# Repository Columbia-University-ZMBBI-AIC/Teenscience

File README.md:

# TeenScience
TennScience Platform
TennScience is a hardware and software platform based in Arduino and Teensy 3.6 for science research involving behavioral neuroscience, robotics, sound analysis, and more.
Testing Hardware

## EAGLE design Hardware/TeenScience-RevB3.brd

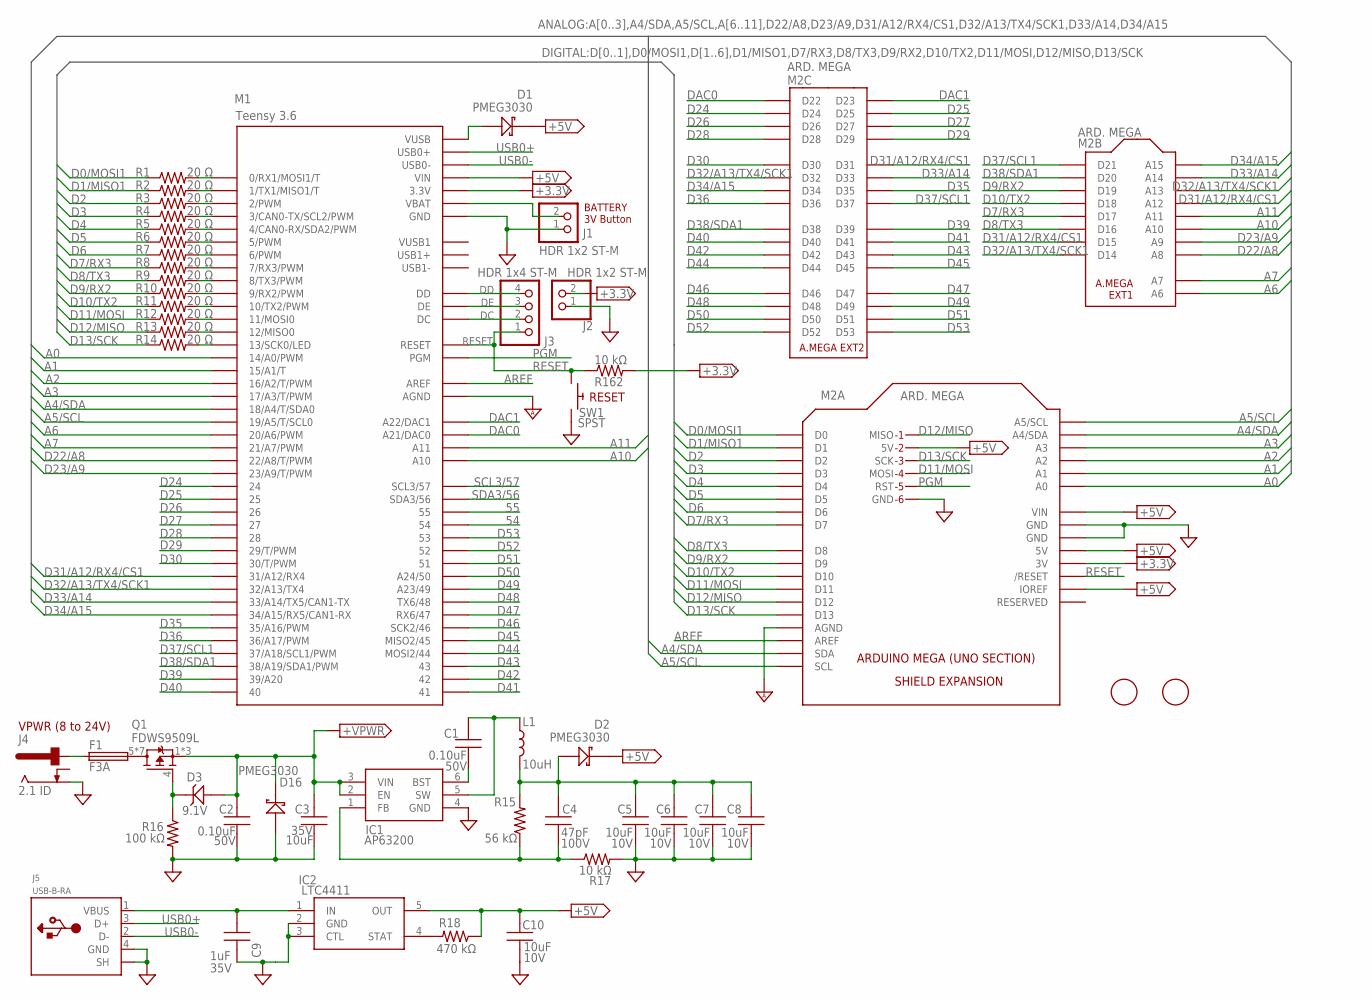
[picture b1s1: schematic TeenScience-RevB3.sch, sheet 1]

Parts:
C1, C2: 0.10uF; MLCC_0603
C3: 10uF; MLCC_1206
C4: 47pF; MLCC_0603
C5, C6, C7, C8, C10: 10uF; MLCC_0603
C9: 1uF; MLCC_0603
D1, D2, D16: PMEG3030; SOD_128_DIODE
D3: 9.1V; SOD3716X135N_DIODE
F1: F3A; 1206-3.2X1.6MM
IC1: AP63200; SOT95P280X100-6N
IC2: LTC4411; SOT95P280X100-5N
J1, J2: HDR 1x2 ST-M; HDR_1X2
J3: HDR 1x4 ST-M; HDR_1X04
J4: 2.1 ID; DCJACK-721RA
J5: USB-B-RA; USB-B
L1: 10uH; IND_5X5MM-5045
M1: Teensy 3.6; TEENSY_3.6_ALL_PINS&PADS
M2: ARD. MEGA; ARDUINO_MEGA_ICSP
Q1: FDWS9509L; FDN8_5.1X6.3
R1, R2, R3, R4, R5, R6, R7, R8, R9, R10, R11, R12, R13, R14: 20 Ω; R0603
R15: 56 kΩ; R0603
R16: 100 kΩ; R0603
R17, R162: 10 kΩ; R0603
R18: 470 kΩ; R0603
SW1: SPST; SWITCH_TAC_6MM
U$3, U$6: FIDUCIAL; FIDUCIAL_1MM

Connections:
54: M1.54; also elsewhere on the board
55: M1.55; also elsewhere on the board
+3.3V: J2.2, M1.3.3V, M1.3.3V2 (3.3V), M1.3.3V3 (3.3V), M1.3.3V4 (3.3V), M2.3V, R162.2; also elsewhere on the board
+5V: C10.2, D1.1 (K), D2.1 (K), IC2.5 (OUT), M1.VIN, M2.5V, M2.5V@1 (5V), M2.5V@2 (5V), M2.5V_ICSP (5V), M2.IOREF, M2.VIN, R18.1; also elsewhere on the board
+VPWR: C2.1, C3.1, D3.2 (A), D16.1 (K), IC1.2 (EN), IC1.3 (VIN), Q1.1 (S), Q1.2 (S), Q1.3 (S); also elsewhere on the board
A0: M1.14/A0 (14/A0/PWM), M2.A0; also elsewhere on the board
A1: M1.15/A1 (15/A1/T), M2.A1; also elsewhere on the board
A2: M1.16/A2 (16/A2/T/PWM), M2.A2; also elsewhere on the board
A3: M1.17/A3 (17/A3/T/PWM), M2.A3; also elsewhere on the board
A4/SDA: M1.18/A4 (18/A4/T/SDA0), M2.A4 (A4/SDA), M2.SDA; also elsewhere on the board
A5/SCL: M1.19/A5 (19/A5/T/SCL0), M2.A5 (A5/SCL), M2.SCL; also elsewhere on the board
A6: M1.20/A6 (20/A6/PWM), M2.A6; also elsewhere on the board
A7: M1.21/A7 (21/A7/PWM), M2.A7; also elsewhere on the board
A10: M1.A10, M2.A10
A11: M1.A11, M2.A11
AREF: M1.AREF, M2.AREF; also elsewhere on the board
D0/MOSI1: M2.D0, R1.1; also elsewhere on the board
D1/MISO1: M2.D1, R2.1; also elsewhere on the board
D2: M2.D2, R3.1; also elsewhere on the board
D3: M2.D3, R4.1; also elsewhere on the board
D4: M2.D4, R5.1; also elsewhere on the board
D5: M2.D5, R6.1; also elsewhere on the board
D6: M2.D6, R7.1; also elsewhere on the board
D7/RX3: M2.D7, M2.D17, R8.1; also elsewhere on the board
D8/TX3: M2.D8, M2.D16, R9.1; also elsewhere on the board
D9/RX2: M2.D9, M2.D19, R10.1; also elsewhere on the board
D10/TX2: M2.D10, M2.D18, R11.1; also elsewhere on the board
D11/MOSI: M2.D11, M2.MOSI, R12.1; also elsewhere on the board
D12/MISO: M2.D12, M2.MISO, R13.1; also elsewhere on the board
D13/SCK: M2.D13, M2.SCK, R14.1; also elsewhere on the board
D22/A8: M1.22/A8 (22/A8/T/PWM), M2.A8; also elsewhere on the board
D23/A9: M1.23/A9 (23/A9/T/PWM), M2.A9; also elsewhere on the board
D24: M1.24, M2.D24; also elsewhere on the board
D25: M1.25, M2.D25; also elsewhere on the board
D26: M1.26, M2.D26; also elsewhere on the board
D27: M1.27, M2.D27; also elsewhere on the board
D28: M1.28, M2.D28; also elsewhere on the board
D29: M1.29 (29/T/PWM), M2.D29; also elsewhere on the board
D30: M1.30 (30/T/PWM), M2.D30; also elsewhere on the board
D31/A12/RX4/CS1: M1.31/A12 (31/A12/RX4), M2.A12, M2.D15, M2.D31; also elsewhere on the board
D32/A13/TX4/SCK1: M1.32/A13 (32/A13/TX4), M2.A13, M2.D14, M2.D32; also elsewhere on the board
D33/A14: M1.33/A14 (33/A14/TX5/CAN1-TX), M2.A14, M2.D33; also elsewhere on the board
D34/A15: M1.34/A15 (34/A15/RX5/CAN1-RX), M2.A15, M2.D34; also elsewhere on the board
D35: M1.35/A16 (35/A16/PWM), M2.D35; also elsewhere on the board
D36: M1.36/A17 (36/A17/PWM), M2.D36; also elsewhere on the board
D37/SCL1: M1.37/A18 (37/A18/SCL1/PWM), M2.D21, M2.D37; also elsewhere on the board
D38/SDA1: M1.38/A19 (38/A19/SDA1/PWM), M2.D20, M2.D38; also elsewhere on the board
D39: M1.39/A20, M2.D39; also elsewhere on the board
D40: M1.40, M2.D40; also elsewhere on the board
D41: M1.41, M2.D41; also elsewhere on the board
D42: M1.42, M2.D42; also elsewhere on the board
D43: M1.43, M2.D43; also elsewhere on the board
D44: M1.44 (MOSI2/44), M2.D44; also elsewhere on the board
D45: M1.45 (MISO2/45), M2.D45; also elsewhere on the board
D46: M1.46 (SCK2/46), M2.D46; also elsewhere on the board
D47: M1.47 (RX6/47), M2.D47; also elsewhere on the board
D48: M1.48 (TX6/48), M2.D48; also elsewhere on the board
D49: M1.49 (A23/49), M2.D49; also elsewhere on the board
D50: M1.50 (A24/50), M2.D50; also elsewhere on the board
D51: M1.51, M2.D51; also elsewhere on the board
D52: M1.52, M2.D52; also elsewhere on the board
D53: M1.53, M2.D53; also elsewhere on the board
DAC0: M1.A21 (A21/DAC0), M2.D22; also elsewhere on the board
DAC1: M1.A22 (A22/DAC1), M2.D23; also elsewhere on the board
DC: J3.2, M1.DC
DD: J3.4, M1.DD
DE: J3.3, M1.DE
GND: C2.2, C3.2, C5.1, C6.1, C7.1, C8.1, C9.2, C10.1, D16.2 (A), IC1.4 (GND), IC2.2 (GND), IC2.3 (CTL), J1.1, J2.1, J4.2 (SLEEVE), J5.4 (GND), J5.5 (SH), J5.6 (SH), M1.GND, M1.GND1 (GND), M1.GND2 (GND), M1.GND3 (GND), M1.GND4 (GND), M1.GND5 (GND), M1.GND6 (GND), M2.GND@1 (GND), M2.GND@2 (GND), M2.GND@3 (GND), M2.GND@4 (GND), M2.GND@5 (GND), R16.2, R17.2, SW1.3, SW1.4; also elsewhere on the board
GND_A: M1.AGND, M2.AGND; also elsewhere on the board
unnamed: D1.2 (A), M1.VUSB
unnamed: C9.1, IC2.1 (IN), J5.1 (VBUS)
unnamed: IC2.4 (STAT), R18.2
unnamed: J1.2, M1.VBAT
unnamed: F1.1, J4.1 (CENTER)
unnamed: C4.2, C5.2, C6.2, C7.2, C8.2, D2.2 (A), L1.2, R15.2
unnamed: F1.2, Q1.5 (D), Q1.6 (D), Q1.7 (D), Q1.8 (D), Q1.9 (D), Q1.10 (D), Q1.11 (D)
unnamed: D3.1 (K), Q1.4 (G), R16.1
unnamed: C1.2, IC1.5 (SW), L1.1
unnamed: C4.1, IC1.1 (FB), R15.1, R17.1
unnamed: C1.1, IC1.6 (BST)
unnamed: M1.13 (13/SCK0/LED), R14.2
unnamed: M1.0 (0/RX1/MOSI1/T), R1.2
unnamed: M1.1 (1/TX1/MISO1/T), R2.2
unnamed: M1.2 (2/PWM), R3.2
unnamed: M1.3 (3/CAN0-TX/SCL2/PWM), R4.2
unnamed: M1.4 (4/CAN0-RX/SDA2/PWM), R5.2
unnamed: M1.5 (5/PWM), R6.2
unnamed: M1.6 (6/PWM), R7.2
unnamed: M1.7 (7/RX3/PWM), R8.2
unnamed: M1.8 (8/TX3/PWM), R9.2
unnamed: M1.9 (9/RX2/PWM), R10.2
unnamed: M1.10 (10/TX2/PWM), R11.2
unnamed: M1.11 (11/MOSI0), R12.2
unnamed: M1.12 (12/MISO0), R13.2
PGM: M1.PGM, M2.RESET_ICSP (RST)
RESET: J3.1, M1.RESET, M2.RESET (/RESET), R162.1, SW1.1, SW1.2; also elsewhere on the board
SCL3/57: M1.57 (SCL3/57); also elsewhere on the board
SDA3/56: M1.56 (SDA3/56); also elsewhere on the board
USB0+: J5.3 (D+), M1.USB0+
USB0-: J5.2 (D-), M1.USB0-
VUSB1: M1.VUSB1

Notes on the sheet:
BATTERY 3V Button
RESET
VPWR (8 to 24V)

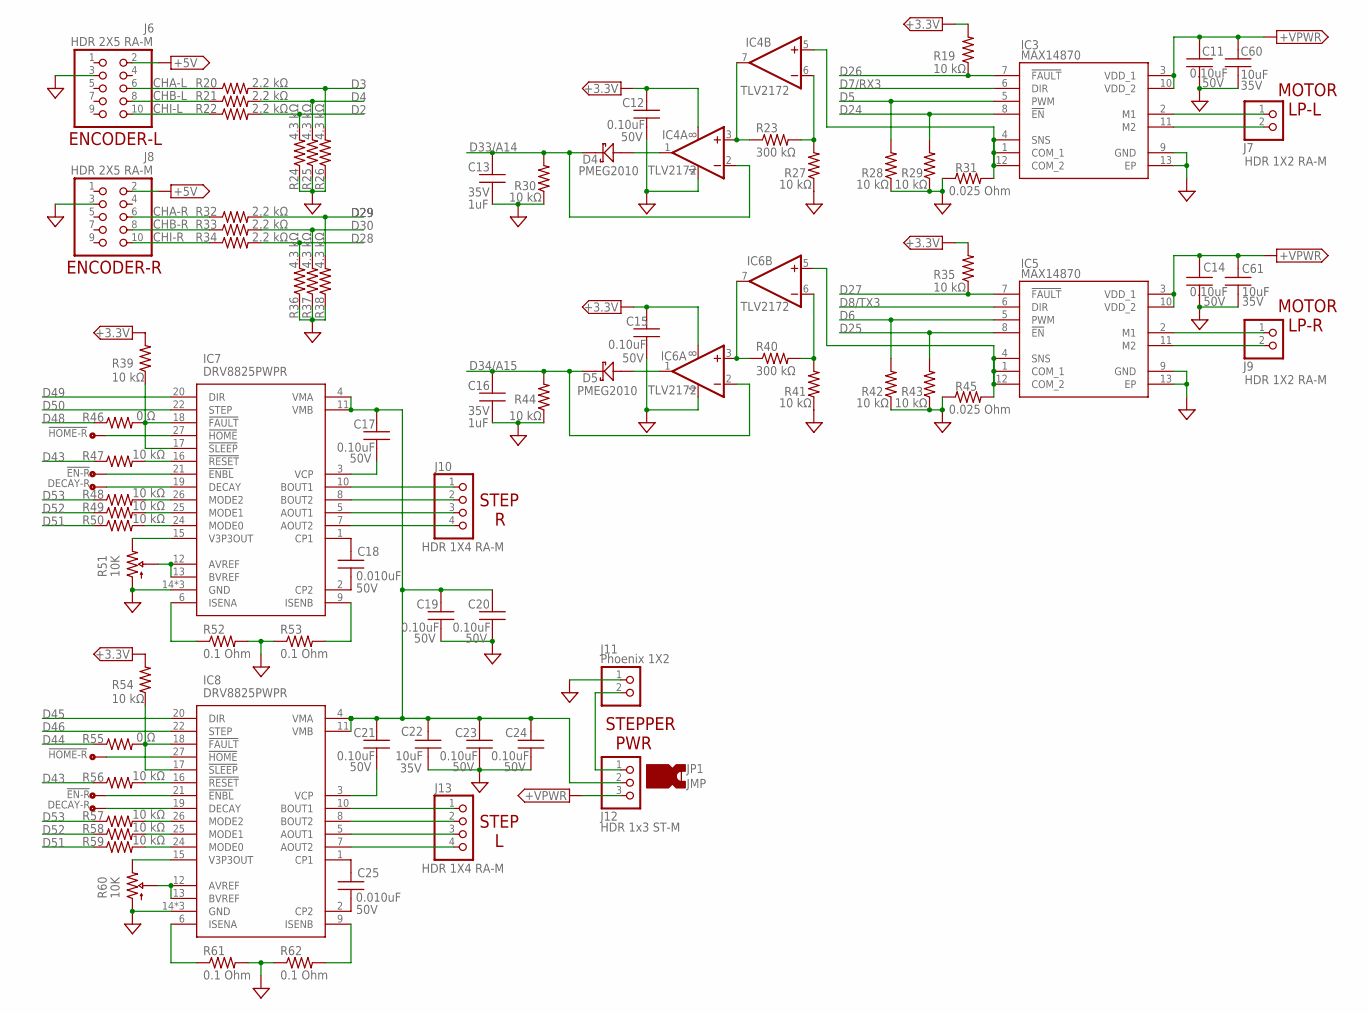
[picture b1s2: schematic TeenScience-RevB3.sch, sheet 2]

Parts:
C11, C12, C14, C15, C17, C19, C20, C21, C23, C24: 0.10uF; MLCC_0603
C13, C16: 1uF; MLCC_0603
C18, C25: 0.010uF; MLCC_0603
C22, C60, C61: 10uF; MLCC_1206
D4, D5: PMEG2010; SOD-123FL
IC3, IC5: MAX14870; TDFN12-EP
IC4, IC6: TLV2172; VSSOP8-DGK-065P
IC7, IC8: DRV8825PWPR; TSSOP28-PWR
J6, J8: HDR 2X5 RA-M; HDR_2X5M_RAS
J7, J9: HDR 1X2 RA-M; HDR_1X2RAS
J10, J13: HDR 1X4 RA-M; HDR_1X4RAS
J11: Phoenix 1X2; TE_282834-2_PHOENIX2
J12: HDR 1x3 ST-M; HDR_1X3
R19, R27, R28, R29, R30, R35, R39, R41, R42, R43, R44, R47, R48, R49, R50, R54, R56, R57, R58, R59: 10 kΩ; R0603
R20, R21, R22, R32, R33, R34: 2.2 kΩ; R0603
R23, R40: 300 kΩ; R0603
R24, R25, R26, R36, R37, R38: 4.3 kΩ; R0603
R31, R45: 0.025 Ohm; R1206
R46, R55: 0 Ω; R0603
R51, R60: 10K; SM-4.5X4.5-TRIM
R52, R53, R61, R62: 0.1 Ohm; R1210
TP1, TP4: !HOME-R; SMT_TEST
TP2, TP5: !EN-R; SMT_TEST
TP3, TP6: DECAY-R; SMT_TEST

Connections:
+3.3V: C12.2, C15.2, IC4.8 (V+), IC6.8 (V+), R19.2, R35.2, R39.2, R54.2; also elsewhere on the board
+5V: J6.2, J8.2; also elsewhere on the board
+VPWR: C11.2, C14.2, C60.1, C61.1, IC3.3 (VDD_1), IC3.10 (VDD_2), IC5.3 (VDD_1), IC5.10 (VDD_2), J12.3; also elsewhere on the board
CHA-L: J6.6, R20.1
CHA-R: J8.6, R32.1
CHB-L: J6.8, R21.1
CHB-R: J8.8, R33.1
CHI-L: J6.10, R22.1
CHI-R: J8.10, R34.1
D2: R22.2, R24.2; also elsewhere on the board
D3: R20.2, R26.2; also elsewhere on the board
D4: R21.2, R25.2; also elsewhere on the board
D5: IC3.5 (PWM), R28.2; also elsewhere on the board
D6: IC5.5 (PWM), R42.2; also elsewhere on the board
D7/RX3: IC3.6 (DIR); also elsewhere on the board
D8/TX3: IC5.6 (DIR); also elsewhere on the board
D24: IC3.8 (!EN), R29.2; also elsewhere on the board
D25: IC5.8 (!EN), R43.2; also elsewhere on the board
D26: IC3.7 (!FAULT), R19.1; also elsewhere on the board
D27: IC5.7 (!FAULT), R35.1; also elsewhere on the board
D28: R34.2, R36.2; also elsewhere on the board
D29: R32.2, R38.2; also elsewhere on the board
D30: R33.2, R37.2; also elsewhere on the board
D33/A14: C13.2, D4.1 (K), IC4.2 (-IN), R30.2; also elsewhere on the board
D34/A15: C16.2, D5.1 (K), IC6.2 (-IN), R44.2; also elsewhere on the board
D43: R47.1, R56.1; also elsewhere on the board
D44: R55.1; also elsewhere on the board
D45: IC8.20 (DIR); also elsewhere on the board
D46: IC8.22 (STEP); also elsewhere on the board
D48: R46.1; also elsewhere on the board
D49: IC7.20 (DIR); also elsewhere on the board
D50: IC7.22 (STEP); also elsewhere on the board
D51: R50.1, R59.1; also elsewhere on the board
D52: R49.1, R58.1; also elsewhere on the board
D53: R48.1, R57.1; also elsewhere on the board
GND: C11.1, C12.1, C13.1, C14.1, C15.1, C16.1, C19.1, C20.1, C22.1, C23.1, C24.1, C60.2, C61.2, IC3.9 (GND), IC3.13 (EP), IC4.4 (V-), IC5.9 (GND), IC5.13 (EP), IC6.4 (V-), IC7.14 (GND), IC7.28 (GND), IC7.29 (GND), IC8.14 (GND), IC8.28 (GND), IC8.29 (GND), J6.3, J8.3, J11.1, R24.1, R25.1, R26.1, R27.1, R28.1, R29.1, R30.1, R31.1, R36.1, R37.1, R38.1, R41.1, R42.1, R43.1, R44.1, R45.1, R51.3 (START), R52.2, R53.1, R60.3 (START), R61.2, R62.1; also elsewhere on the board
unnamed: IC5.2 (M1), J9.1
unnamed: IC5.11 (M2), J9.2
unnamed: D5.2 (A), IC6.1 (OUT)
unnamed: IC6.6 (-IN), R40.2, R41.2
unnamed: IC5.1 (COM_1), IC5.4 (SNS), IC5.12 (COM_2), IC6.5 (+IN), R45.2
unnamed: IC3.2 (M1), J7.1
unnamed: IC6.3 (+IN), IC6.7 (OUT), R40.1
unnamed: IC3.11 (M2), J7.2
unnamed: IC3.1 (COM_1), IC3.4 (SNS), IC3.12 (COM_2), IC4.5 (+IN), R31.2
unnamed: D4.2 (A), IC4.1 (OUT)
unnamed: IC4.6 (-IN), R23.2, R27.2
unnamed: IC4.3 (+IN), IC4.7 (OUT), R23.1
unnamed: J11.2, J12.1
unnamed: IC8.15 (V3P3OUT), R60.1 (END)
unnamed: IC8.12 (AVREF), IC8.13 (BVREF), R60.2 (WIPER)
unnamed: IC8.6 (ISENA), R61.1
unnamed: C21.1, IC8.3 (VCP)
unnamed: IC8.9 (ISENB), R62.2
unnamed: C25.1, IC8.2 (CP2)
unnamed: C25.2, IC8.1 (CP1)
unnamed: IC8.10 (BOUT1), J13.1
unnamed: IC8.8 (BOUT2), J13.2
unnamed: IC8.5 (AOUT1), J13.3
unnamed: IC8.7 (AOUT2), J13.4
unnamed: IC8.27 (!HOME), TP1.NC1, TP1.NC2, TP1.NC3, TP1.TP
unnamed: IC8.24 (MODE0), R59.2
unnamed: IC8.25 (MODE1), R58.2
unnamed: IC8.26 (MODE2), R57.2
unnamed: C17.2, C19.2, C20.2, C21.2, C22.2, C23.2, C24.2, IC7.4 (VMA), IC7.11 (VMB), IC8.4 (VMA), IC8.11 (VMB), J12.2
unnamed: IC7.12 (AVREF), IC7.13 (BVREF), R51.2 (WIPER)
unnamed: IC7.6 (ISENA), R52.1
unnamed: IC8.17 (!SLEEP), IC8.18 (!FAULT), R54.1, R55.2
unnamed: IC7.9 (ISENB), R53.2
unnamed: C18.1, IC7.2 (CP2)
unnamed: C18.2, IC7.1 (CP1)
unnamed: IC7.15 (V3P3OUT), R51.1 (END)
unnamed: IC8.19 (DECAY), TP3.NC1, TP3.NC2, TP3.NC3, TP3.TP
unnamed: IC8.21 (!ENBL), TP2.NC1, TP2.NC2, TP2.NC3, TP2.TP
unnamed: IC8.16 (!RESET), R56.2
unnamed: C17.1, IC7.3 (VCP)
unnamed: IC7.10 (BOUT1), J10.1
unnamed: IC7.8 (BOUT2), J10.2
unnamed: IC7.5 (AOUT1), J10.3
unnamed: IC7.7 (AOUT2), J10.4
unnamed: IC7.27 (!HOME), TP4.NC1, TP4.NC2, TP4.NC3, TP4.TP
unnamed: IC7.24 (MODE0), R50.2
unnamed: IC7.25 (MODE1), R49.2
unnamed: IC7.26 (MODE2), R48.2
unnamed: IC7.17 (!SLEEP), IC7.18 (!FAULT), R39.1, R46.2
unnamed: IC7.19 (DECAY), TP6.NC1, TP6.NC2, TP6.NC3, TP6.TP
unnamed: IC7.21 (!ENBL), TP5.NC1, TP5.NC2, TP5.NC3, TP5.TP
unnamed: IC7.16 (!RESET), R47.2

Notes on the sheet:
MOTOR LP-R
ENCODER-L
ENCODER-R
MOTOR LP-L
STEPPER PWR
STEP R
STEP L

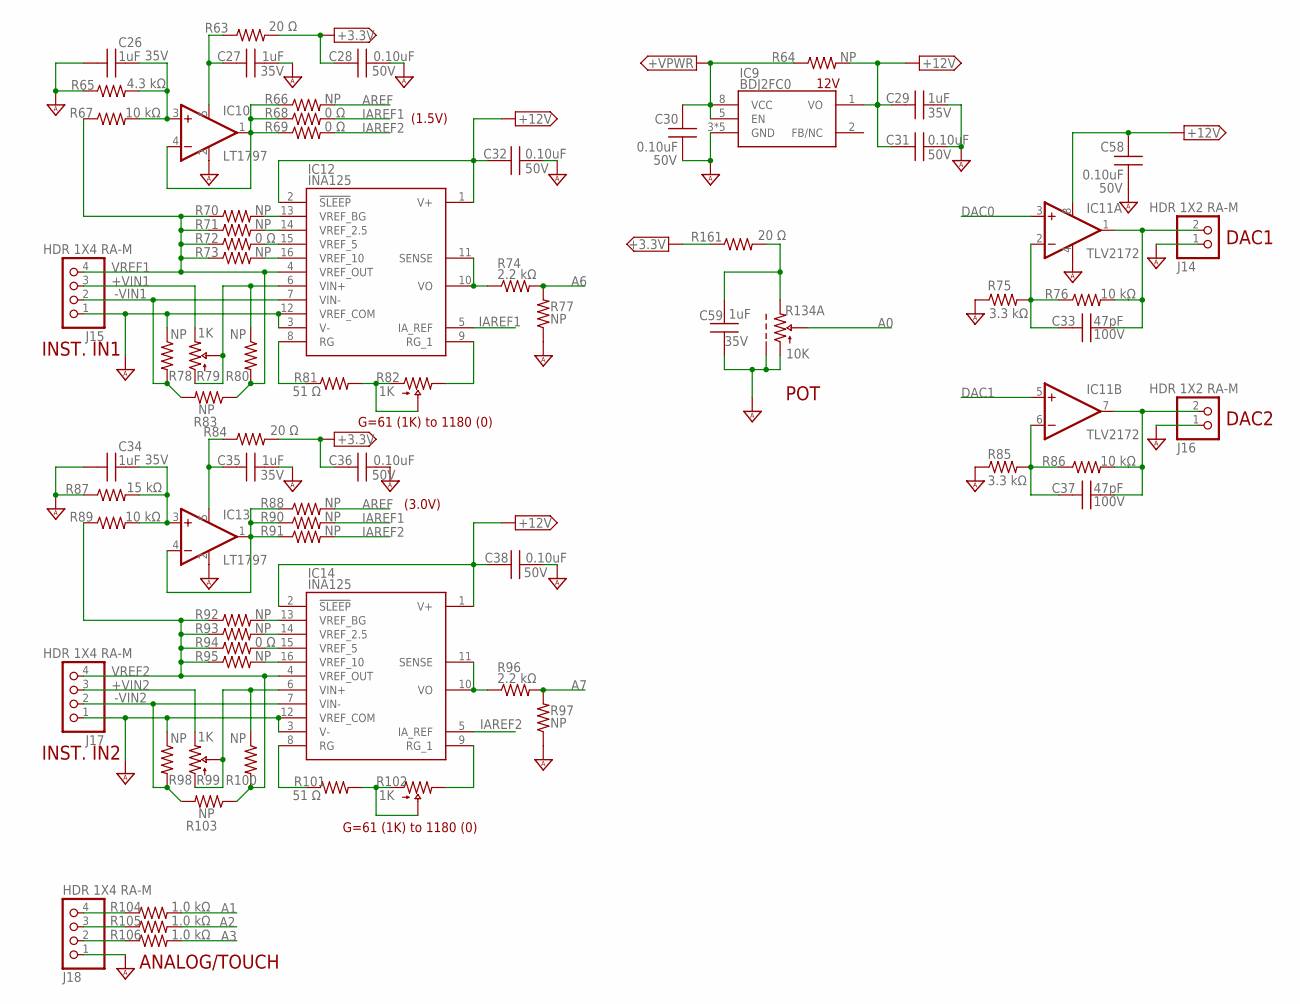
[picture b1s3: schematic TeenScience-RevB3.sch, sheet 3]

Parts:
C26, C27, C29, C34, C35, C59: 1uF; MLCC_0603
C28, C30, C31, C32, C36, C38, C58: 0.10uF; MLCC_0603
C33, C37: 47pF; MLCC_0603
IC9: BDJ2FC0; SOIC8-PAD127P600X100
IC10, IC13: LT1797; SOT23-5
IC11: TLV2172; VSSOP8-DGK-065P
IC12, IC14: INA125; SOIC16-127P600X175
J14, J16: HDR 1X2 RA-M; HDR_1X2RAS
J15, J17, J18: HDR 1X4 RA-M; HDR_1X4RAS
R63, R84, R161: 20 Ω; R0603
R64, R66, R70, R71, R73, R77, R78, R80, R83, R88, R90, R91, R92, R93, R95, R97, R98, R100, R103: NP; R0603
R65: 4.3 kΩ; R0603
R67, R76, R86, R89: 10 kΩ; R0603
R68, R69, R72, R94: 0 Ω; R0603
R74, R96: 2.2 kΩ; R0603
R75, R85: 3.3 kΩ; R0603
R79, R82, R99, R102: 1K; PV36YTRIMMER
R81, R101: 51 Ω; R0603
R87: 15 kΩ; R0603
R104, R105, R106: 1.0 kΩ; R0603
R134: 10K; RK09-ALPS-VERT-POT

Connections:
+3.3V: C28.2, C36.2, R63.2, R84.2, R161.1; also elsewhere on the board
+12V: C29.1, C31.2, C32.2, C38.2, C58.2, IC9.1 (VO), IC11.8 (V+), IC12.1 (V+), IC12.2 (!SLEEP), IC14.1 (V+), IC14.2 (!SLEEP), R64.2
+VIINDIR1: IC12.6 (VIN+), R79.1 (START), R79.2 (WIPER), R80.1
+VIINDIR2: IC14.6 (VIN+), R99.1 (START), R99.2 (WIPER), R100.1
+VIN1: J15.3, R79.3 (END)
+VIN2: J17.3, R99.3 (END)
+VPWR: C30.2, IC9.5 (EN), IC9.8 (VCC), R64.1; also elsewhere on the board
-VIN1: IC12.7 (VIN-), J15.2, R78.2, R83.2
-VIN2: IC14.7 (VIN-), J17.2, R98.2, R103.2
A0: R134.2 (WIPER); also elsewhere on the board
A1: R104.2; also elsewhere on the board
A2: R105.2; also elsewhere on the board
A3: R106.2; also elsewhere on the board
A6: R74.2, R77.2; also elsewhere on the board
A7: R96.2, R97.2; also elsewhere on the board
AREF: R66.2, R88.2; also elsewhere on the board
DAC0: IC11.3 (+IN); also elsewhere on the board
DAC1: IC11.5 (+IN); also elsewhere on the board
GND_A: C26.1, C27.1, C28.1, C29.2, C30.1, C31.1, C32.1, C34.1, C35.1, C36.1, C38.1, C58.1, C59.2, IC9.3 (GND), IC9.4 (GND), IC9.6 (GND), IC9.7 (GND), IC9.9 (GND), IC10.2 (V-), IC11.4 (V-), IC12.3 (V-), IC12.12 (VREF_COM), IC13.2 (V-), IC14.3 (V-), IC14.12 (VREF_COM), J14.1, J15.1, J16.1, J17.1, J18.1, R65.1, R75.1, R77.1, R78.1, R85.1, R87.1, R97.1, R98.1, R134.1 (START), R134.MH1 (SHELL), R134.MH2 (SHELL); also elsewhere on the board
IAREF1: IC12.5 (IA_REF), R68.2, R90.2
IAREF2: IC14.5 (IA_REF), R69.2, R91.2
unnamed: C27.2, IC10.5 (V+), R63.1
unnamed: C59.1, R134.3 (END), R161.2
unnamed: J18.4, R104.1
unnamed: J18.3, R105.1
unnamed: J18.2, R106.1
unnamed: IC12.10 (VO), IC12.11 (SENSE), R74.1
unnamed: IC12.13 (VREF_BG), R70.2
unnamed: C26.2, IC10.3 (+IN), R65.2, R67.2
unnamed: IC10.1 (OUT), IC10.4 (-IN), R66.1, R68.1, R69.1
unnamed: R81.2, R82.1 (START), R82.2 (WIPER)
unnamed: IC12.14 (VREF_2.5), R71.2
unnamed: IC12.15 (VREF_5), R72.2
unnamed: IC12.16 (VREF_10), R73.2
unnamed: R101.2, R102.1 (START), R102.2 (WIPER)
unnamed: IC12.8 (RG), R81.1
unnamed: IC12.9 (RG_1), R82.3 (END)
unnamed: IC14.14 (VREF_2.5), R93.2
unnamed: IC14.15 (VREF_5), R94.2
unnamed: IC14.16 (VREF_10), R95.2
unnamed: IC14.8 (RG), R101.1
unnamed: IC14.9 (RG_1), R102.3 (END)
unnamed: IC14.13 (VREF_BG), R92.2
unnamed: IC14.10 (VO), IC14.11 (SENSE), R96.1
unnamed: C34.2, IC13.3 (+IN), R87.2, R89.2
unnamed: IC13.1 (OUT), IC13.4 (-IN), R88.1, R90.1, R91.1
unnamed: C35.2, IC13.5 (V+), R84.1
unnamed: C33.1, IC11.2 (-IN), R75.2, R76.1
unnamed: C33.2, IC11.1 (OUT), J14.2, R76.2
unnamed: C37.1, IC11.6 (-IN), R85.2, R86.1
unnamed: C37.2, IC11.7 (OUT), J16.2, R86.2
VREF1: IC12.4 (VREF_OUT), J15.4, R67.1, R70.1, R71.1, R72.1, R73.1, R80.2, R83.1
VREF2: IC14.4 (VREF_OUT), J17.4, R89.1, R92.1, R93.1, R94.1, R95.1, R100.2, R103.1

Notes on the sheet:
INST. IN1
INST. IN2
(3.0V)
(1.5V)
12V
DAC1
DAC2
ANALOG/TOUCH
POT
G=61 (1K) to 1180 (0)

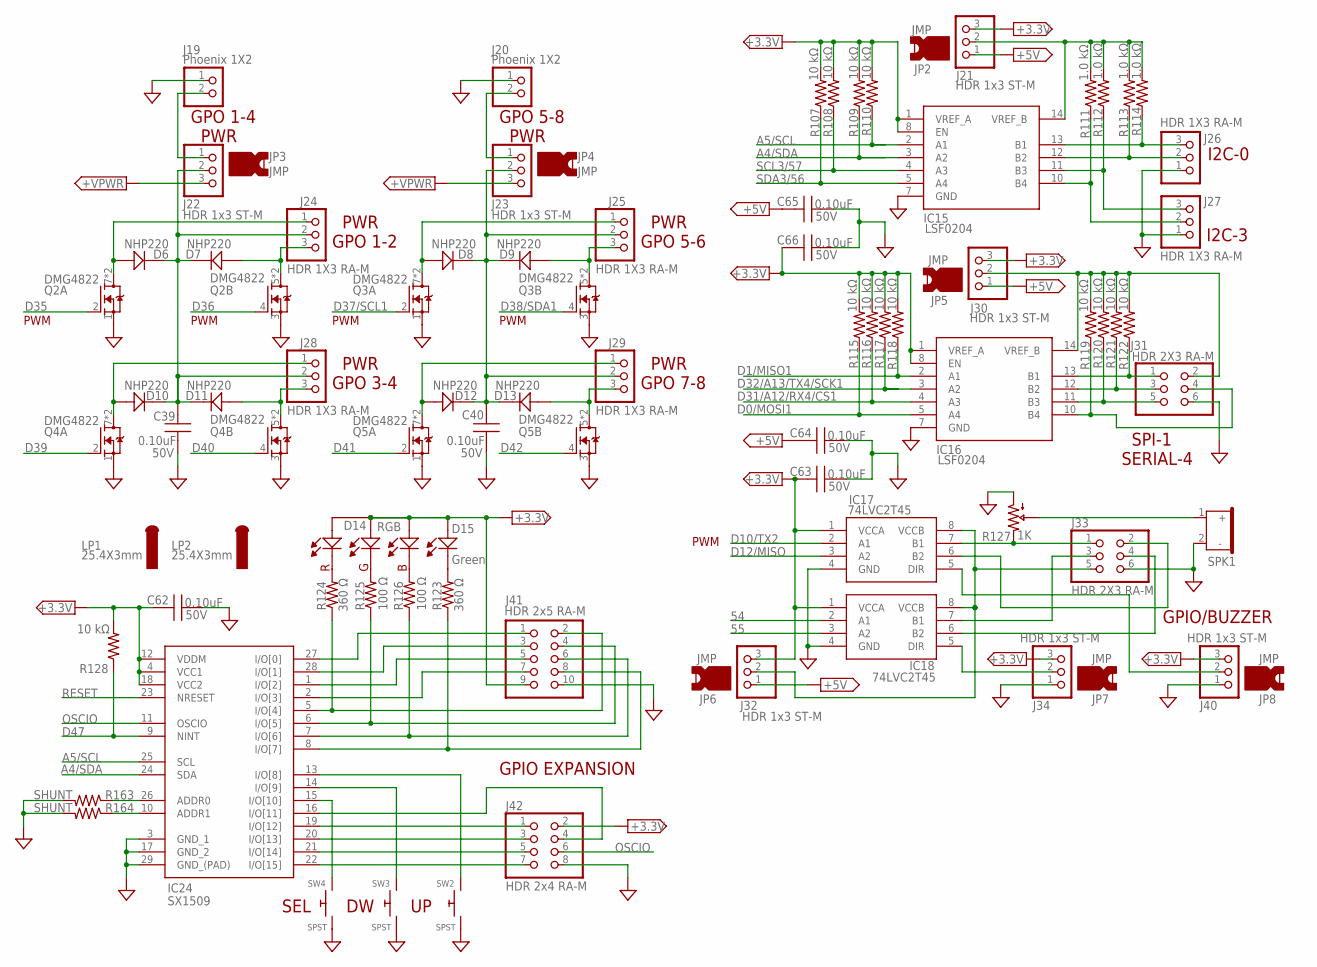
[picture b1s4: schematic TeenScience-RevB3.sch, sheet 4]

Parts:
C39, C40, C62, C63, C64, C65, C66: 0.10uF; MLCC_0603
D6, D7, D8, D9, D10, D11, D12, D13: NHP220; SOD-123FL
D14: RGB; SON95P2X2X1-RGB_LED
D15: Green; LED_0603
IC15, IC16: LSF0204; TSSOP14
IC17, IC18: 74LVC2T45; VSSOP8-DCU-050P
IC24: SX1509; QFN-28-4MM-0.4P-PAD
J19, J20: Phoenix 1X2; TE_282834-2_PHOENIX2
J21, J22, J23, J30, J32, J34, J40: HDR 1x3 ST-M; HDR_1X3
J24, J25, J26, J27, J28, J29: HDR 1X3 RA-M; HDR_1X3RAS
J31, J33: HDR 2X3 RA-M; HDR_2X3M_RAS
J41: HDR 2x5 RA-M; HDR_2X5M-RAHDR
J42: HDR 2x4 RA-M; HDR_2X4M-RAHDR
LP1, LP2: 25.4X3mm; EXTERNAL
Q2, Q3, Q4, Q5: DMG4822; SOIC8-127P60
R107, R108, R109, R110, R115, R116, R117, R118, R119, R120, R121, R122, R128: 10 kΩ; R0603
R111, R112, R113, R114: 1.0 kΩ; R0603
R123, R124: 360 Ω; R0603
R125, R126: 100 Ω; R0603
R127: 1K; SM-4.5X4.5-TRIM
R163, R164: SHUNT; R0603-SHORT
SPK1: CMI-9650C-120; BUZZER-5MM-12.4D
SW2, SW3, SW4: SPST; SWITCH_TAC_6MM

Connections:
1: IC15.13 (B1), J26.3, R114.1
2: IC15.12 (B2), J26.2, R113.1
3: IC16.13 (B1), J31.1, R122.1
4: IC16.12 (B2), J31.3, R121.1
54: IC18.2 (A1); also elsewhere on the board
55: IC18.3 (A2); also elsewhere on the board
+3.3V: C62.2, C63.2, C66.2, D14.1 (CA), D15.2 (A), IC15.1 (VREF_A), IC15.8 (EN), IC16.1 (VREF_A), IC16.8 (EN), IC17.1 (VCCA), IC18.1 (VCCA), IC24.4 (VCC1), IC24.12 (VDDM), IC24.18 (VCC2), J21.3, J30.3, J32.3, J34.3, J40.3, J41.9, J42.2, R107.2, R108.2, R109.2, R110.2, R115.2, R116.2, R117.2, R118.2, R128.2; also elsewhere on the board
+5V: C64.2, C65.2, J21.1, J30.1, J32.1; also elsewhere on the board
+VPWR: J22.3, J23.3; also elsewhere on the board
A4/SDA: IC15.3 (A2), IC24.24 (SDA), R109.1; also elsewhere on the board
A5/SCL: IC15.2 (A1), IC24.25 (SCL), R110.1; also elsewhere on the board
D0/MOSI1: IC16.5 (A4), R115.1; also elsewhere on the board
D1/MISO1: IC16.2 (A1), R118.1; also elsewhere on the board
D10/TX2: IC17.2 (A1); also elsewhere on the board
D12/MISO: IC17.3 (A2); also elsewhere on the board
D31/A12/RX4/CS1: IC16.4 (A3), R116.1; also elsewhere on the board
D32/A13/TX4/SCK1: IC16.3 (A2), R117.1; also elsewhere on the board
D35: Q2.2 (G); also elsewhere on the board
D36: Q2.4 (G); also elsewhere on the board
D37/SCL1: Q3.2 (G); also elsewhere on the board
D38/SDA1: Q3.4 (G); also elsewhere on the board
D39: Q4.2 (G); also elsewhere on the board
D40: Q4.4 (G); also elsewhere on the board
D41: Q5.2 (G); also elsewhere on the board
D42: Q5.4 (G); also elsewhere on the board
D47: IC24.9 (NINT), R128.1; also elsewhere on the board
GND: C39.1, C40.1, C62.1, C63.1, C64.1, C65.1, C66.1, IC15.7 (GND), IC16.7 (GND), IC17.4 (GND), IC18.4 (GND), IC24.3 (GND_1), IC24.17 (GND_2), IC24.29 (GND_(PAD)), J19.1, J20.1, J26.1, J27.1, J31.6, J33.6, J34.1, J40.1, J41.10, J42.8, Q2.1 (S), Q2.3 (S), Q3.1 (S), Q3.3 (S), Q4.1 (S), Q4.3 (S), Q5.1 (S), Q5.3 (S), R127.3 (START), R163.2, R163.P$2 (2), R164.2, R164.P$2 (2), SPK1.2 (-), SW2.1, SW2.2, SW3.1, SW3.2, SW4.1, SW4.2; also elsewhere on the board
unnamed: IC15.11 (B3), J27.3, R112.1
unnamed: IC15.10 (B4), J27.2, R111.1
unnamed: IC15.14 (VREF_B), J21.2, R111.2, R112.2, R113.2, R114.2
unnamed: D15.1 (K), R123.2
unnamed: D14.3 (G), R125.2
unnamed: IC17.5 (DIR), J40.2
unnamed: IC17.7 (B1), J33.1, R127.1 (END)
unnamed: J20.2, J23.1
unnamed: D7.2 (A), J24.3, Q2.5 (D), Q2.6 (D)
unnamed: J19.2, J22.1
unnamed: C39.2, D6.1 (K), D7.1 (K), D10.1 (K), D11.1 (K), J22.2, J24.2, J28.2
unnamed: D11.2 (A), J28.3, Q4.5 (D), Q4.6 (D)
unnamed: D10.2 (A), J28.1, Q4.7 (D), Q4.8 (D)
unnamed: D6.2 (A), J24.1, Q2.7 (D), Q2.8 (D)
unnamed: C40.2, D8.1 (K), D9.1 (K), D12.1 (K), D13.1 (K), J23.2, J25.2, J29.2
unnamed: D13.2 (A), J29.3, Q5.5 (D), Q5.6 (D)
unnamed: D12.2 (A), J29.1, Q5.7 (D), Q5.8 (D)
unnamed: D9.2 (A), J25.3, Q3.5 (D), Q3.6 (D)
unnamed: D8.2 (A), J25.1, Q3.7 (D), Q3.8 (D)
unnamed: IC16.10 (B4), J31.4, R119.1
unnamed: IC16.11 (B3), J31.5, R120.1
unnamed: IC16.14 (VREF_B), J30.2, J31.2, R119.2, R120.2, R121.2, R122.2
unnamed: D14.4 (R), R124.2
unnamed: D14.2 (B), R126.2
unnamed: IC24.5 (I/O[4]), J41.2, R124.1
unnamed: IC24.6 (I/O[5]), J41.4, R125.1
unnamed: IC24.7 (I/O[6]), J41.6, R126.1
unnamed: IC24.8 (I/O[7]), J41.8, R123.1
unnamed: IC24.13 (I/O[8]), SW2.3, SW2.4
unnamed: IC24.14 (I/O[9]), SW3.3, SW3.4
unnamed: IC24.15 (I/O[10]), SW4.3, SW4.4
unnamed: IC17.6 (B2), J33.2
unnamed: R127.2 (WIPER), SPK1.1 (+)
unnamed: IC18.5 (DIR), J34.2
unnamed: IC18.7 (B1), J33.3
unnamed: IC18.6 (B2), J33.4
unnamed: IC24.27 (I/O[0]), J41.1
unnamed: IC17.8 (VCCB), IC18.8 (VCCB), J32.2, J33.5
unnamed: IC24.28 (I/O[1]), J41.3
unnamed: IC24.1 (I/O[2]), J41.5
unnamed: IC24.2 (I/O[3]), J41.7
unnamed: IC24.19 (I/O[12]), J42.1
unnamed: IC24.20 (I/O[13]), J42.3
unnamed: IC24.16 (I/O[11]), J42.4
unnamed: IC24.21 (I/O[14]), J42.5
unnamed: IC24.22 (I/O[15]), J42.7
unnamed: IC24.26 (ADDR0), R163.1, R163.P$1 (1)
unnamed: IC24.10 (ADDR1), R164.1, R164.P$1 (1)
OSCIO: IC24.11 (OSCIO), J42.6
RESET: IC24.23 (NRESET); also elsewhere on the board
SCL3/57: IC15.4 (A3), R108.1; also elsewhere on the board
SDA3/56: IC15.5 (A4), R107.1; also elsewhere on the board

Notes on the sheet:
SPI-1 SERIAL-4
GPO 1-4 PWR
GPO 5-8 PWR
PWR GPO 1-2
PWR GPO 3-4
PWR GPO 5-6
PWR GPO 7-8
I2C-3
I2C-0
GPIO/BUZZER
PWM
SEL
GPIO EXPANSION

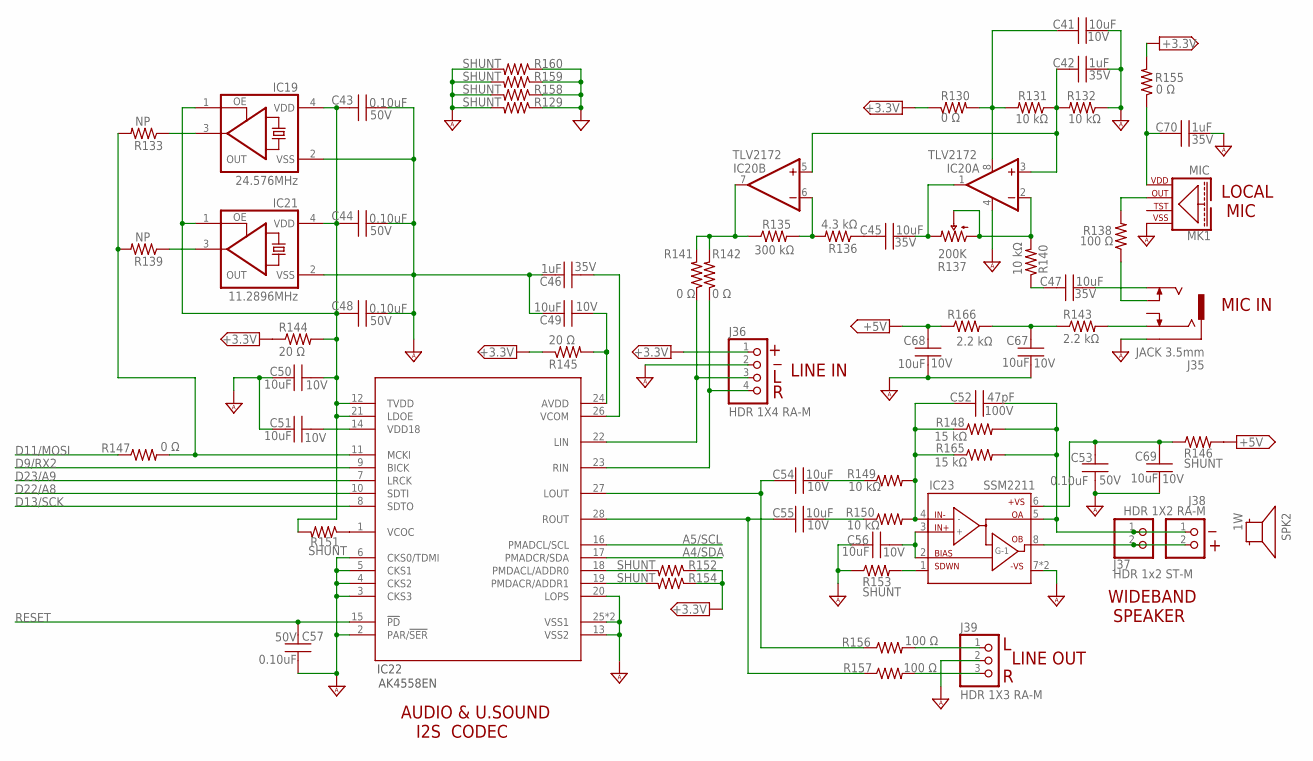
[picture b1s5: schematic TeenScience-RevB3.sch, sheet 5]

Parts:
C41, C49, C50, C51, C54, C55, C56, C67, C68, C69: 10uF; MLCC_0603
C42, C46, C70: 1uF; MLCC_0603
C43, C44, C48, C53, C57: 0.10uF; MLCC_0603
C45, C47: 10uF; MLCC_1206
C52: 47pF; MLCC_0603
IC19: 24.576MHz; 2.5X2-4-PAD
IC20: TLV2172; VSSOP8-DGK-065P
IC21: 11.2896MHz; 2.5X2-4-PAD
IC22: AK4558EN; QFN-28-5MM-0.5P-PAD
IC23: SSM2211; LFCSP8_3X3
J35: JACK 3.5mm; AUDIO-JACK-SJ1-3533NS
J36: HDR 1X4 RA-M; HDR_1X4RAS
J37: HDR 1x2 ST-M; HDR_1X2
J38: HDR 1X2 RA-M; HDR_1X2RAS
J39: HDR 1X3 RA-M; HDR_1X3RAS
MK1: MIC; SPH6611_MEMS_2.65X3.50
R129, R146, R151, R152, R153, R154, R158, R159, R160: SHUNT; R0603-SHORT
R130, R141, R142, R147, R155: 0 Ω; R0603
R131, R132, R140, R149, R150: 10 kΩ; R0603
R133, R139: NP; R0603
R135: 300 kΩ; R0603
R136: 4.3 kΩ; R0603
R137: 200K; SM-4.5X4.5-TRIM
R138, R156, R157: 100 Ω; R0603
R143, R166: 2.2 kΩ; R0603
R144, R145: 20 Ω; R0603
R148, R165: 15 kΩ; R0603
SPK2: 1W; EXTERNAL

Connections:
+3.3V: J36.1, R130.1, R144.1, R145.1, R152.1, R152.P$1 (1), R154.1, R154.P$1 (1), R155.2; also elsewhere on the board
+5V: C68.2, R146.2, R146.P$2 (2), R166.1; also elsewhere on the board
A4/SDA: IC22.17 (PMADCR/SDA); also elsewhere on the board
A5/SCL: IC22.16 (PMADCL/SCL); also elsewhere on the board
D9/RX2: IC22.9 (BICK); also elsewhere on the board
D11/MOSI: R147.1; also elsewhere on the board
D13/SCK: IC22.8 (SDTO); also elsewhere on the board
D22/A8: IC22.10 (SDTI); also elsewhere on the board
D23/A9: IC22.7 (LRCK); also elsewhere on the board
GND: R129.1, R129.P$1 (1), R158.1, R158.P$1 (1), R159.1, R159.P$1 (1), R160.1, R160.P$1 (1); also elsewhere on the board
GND_A: C41.2, C42.2, C43.1, C44.1, C46.2, C48.1, C49.2, C50.2, C51.2, C53.2, C56.1, C57.1, C67.1, C68.1, C69.1, C70.2, IC19.2 (VSS), IC20.4 (V-), IC21.2 (VSS), IC22.2 (PAR/!SER), IC22.3 (CKS3), IC22.4 (CKS2), IC22.5 (CKS1), IC22.6 (CKS0/TDMI), IC22.13 (VSS2), IC22.20 (LOPS), IC22.25 (VSS1), IC22.29 (VSS1), IC23.7 (-VS), IC23.EXP (-VS), J35.1 (SLEEVE), J36.2, J39.2, MK1.2 (VSS), MK1.3 (VSS), R129.2, R129.P$2 (2), R132.1, R153.1, R153.P$1 (1), R158.2, R158.P$2 (2), R159.2, R159.P$2 (2), R160.2, R160.P$2 (2); also elsewhere on the board
unnamed: IC23.8 (OUTB), J37.2, J38.2
unnamed: C46.1, IC22.26 (VCOM)
unnamed: C49.1, IC22.24 (AVDD), R145.2
unnamed: C43.2, C44.2, C48.2, C50.1, IC19.1 (CON), IC19.4 (VDD), IC21.1 (CON), IC21.4 (VDD), IC22.12 (TVDD), IC22.21 (LDOE), R144.2, R151.2, R151.P$2 (2)
unnamed: C51.1, IC22.14 (VDD18)
unnamed: IC22.1 (VCOC), R151.1, R151.P$1 (1)
unnamed: C70.1, MK1.5 (VDD), R155.1
unnamed: IC23.1 (SDWN), R153.2, R153.P$2 (2)
unnamed: C56.2, IC23.2 (BIAS), IC23.3 (IN+)
unnamed: C52.2, IC23.5 (OUTA), J37.1, J38.1, R148.2, R165.2
unnamed: C52.1, IC23.4 (IN-), R148.1, R149.2, R150.2, R165.1
unnamed: IC22.11 (MCKI), R133.2, R139.2, R147.2
unnamed: IC22.18 (PMDACL/ADDR0), R152.2, R152.P$2 (2)
unnamed: IC22.19 (PMDACR/ADDR1), R154.2, R154.P$2 (2)
unnamed: C55.2, R150.1
unnamed: IC21.3 (OUT), R139.1
unnamed: IC19.3 (OUT), R133.1
unnamed: C54.2, R149.1
unnamed: C55.1, IC22.28 (ROUT), R157.1
unnamed: C54.1, IC22.27 (LOUT), R156.1
unnamed: C53.1, C69.2, IC23.6 (+VS), R146.1, R146.P$1 (1)
unnamed: J39.3, R157.2
unnamed: J39.1, R156.2
unnamed: C47.1, R140.1
unnamed: IC22.23 (RIN), J36.4, R142.1
unnamed: IC22.22 (LIN), J36.3, R141.1
unnamed: C47.2, J35.2 (TIP)
unnamed: IC20.2 (-IN), R137.2 (WIPER), R137.3 (START), R140.2
unnamed: C45.1, R136.1
unnamed: C45.2, IC20.1 (OUT), R137.1 (END)
unnamed: IC20.6 (-IN), R135.2, R136.2
unnamed: IC20.7 (OUT), R135.1, R141.2, R142.2
unnamed: C41.1, IC20.8 (V+), R130.2, R131.2
unnamed: C42.1, IC20.3 (+IN), IC20.5 (+IN), R131.1, R132.2
unnamed: J35.4 (SW_TIP), R138.1
unnamed: J35.3 (RING), R143.2
unnamed: MK1.1 (OUT), R138.2
unnamed: C67.2, R143.1, R166.2
RESET: C57.2, IC22.15 (!PD); also elsewhere on the board

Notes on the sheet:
AUDIO & U.SOUND I2S CODEC
WIDEBAND SPEAKER
LINE OUT
LINE IN
MIC IN
LOCAL MIC
